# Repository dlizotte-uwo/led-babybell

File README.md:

# led-babybell
LED driver board that plugs into a Pico. Constant current buck using LM3405 and has STEMMA QT connector.

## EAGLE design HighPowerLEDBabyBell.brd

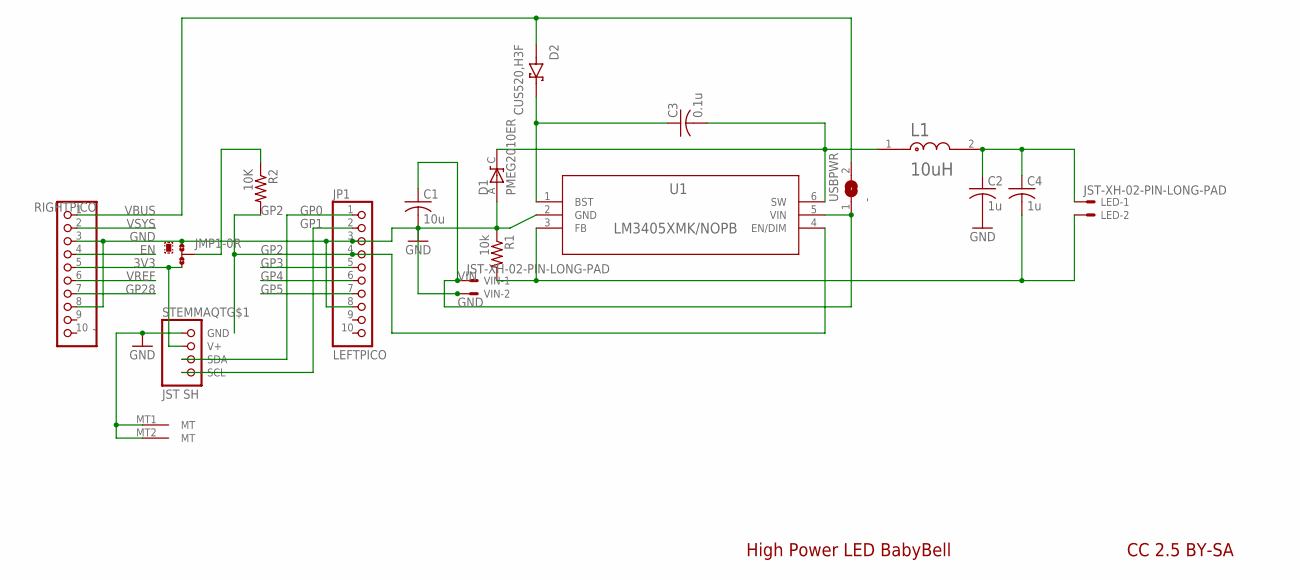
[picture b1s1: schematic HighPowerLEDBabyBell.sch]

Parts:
C1: 10u; C1206
C2, C4: 1u; C1206
C3: 0.1u; C1206
D1: PMEG2010ER; SODFL3517X110N
D2: CUS520,H3F; DIO_CUS520,H3F
JMP1: 0R-JUMPA; A0R-JMP
JP1: LEFTPICO; 1X10
L1: TDK_VLS5045EX-100MTDK_VLS5045EX-100M_0_0; TDK_VLS5045EX-100M_0
LED: JST-XH-02-PIN-LONG-PAD; JST-XH-02-PACKAGE-LONG-PAD
R1: 10k; R1206
R2: 10K; R1206
RIGHTPICO: -; 1X10
STEMMAQT: JST SH; JST_SH4_RA
U1: LM3405XMK/NOPB; MK06A
USBPWR: -; SJ
VIN: JST-XH-02-PIN-LONG-PAD; JST-XH-02-PACKAGE-LONG-PAD

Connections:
3V3: JMP1.3, RIGHTPICO.5, STEMMAQT.2 (V+)
BST: C3.1, D2.C, U1.1 (BST)
EN: RIGHTPICO.4
FB: C4.2, LED.2, R1.2, U1.3 (FB)
GND: C1.2, C2.2, D1.A, JMP1.1, JP1.3, JP1.8, R1.1, RIGHTPICO.3, RIGHTPICO.8, STEMMAQT.1 (GND), STEMMAQT.MT1 (MT), STEMMAQT.MT2 (MT), U1.2 (GND), VIN.2
GP0: JP1.1, STEMMAQT.3 (SDA)
GP1: JP1.2, STEMMAQT.4 (SCL)
GP2: JP1.4, R2.2, U1.4 (EN/DIM)
GP3: JP1.5
GP4: JP1.6
GP5: JP1.7
GP28: RIGHTPICO.7
LED+: C2.1, C4.1, L1.2, LED.1
PUL: JMP1.2, R2.1
SW: C3.2, D1.C, L1.1, U1.6 (SW)
VBUS: D2.A, RIGHTPICO.1, USBPWR.2
VIN: C1.1, U1.5 (VIN), USBPWR.1, VIN.1
VREF: RIGHTPICO.6
VSYS: RIGHTPICO.2

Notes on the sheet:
High Power LED BabyBell
CC 2.5 BY-SA

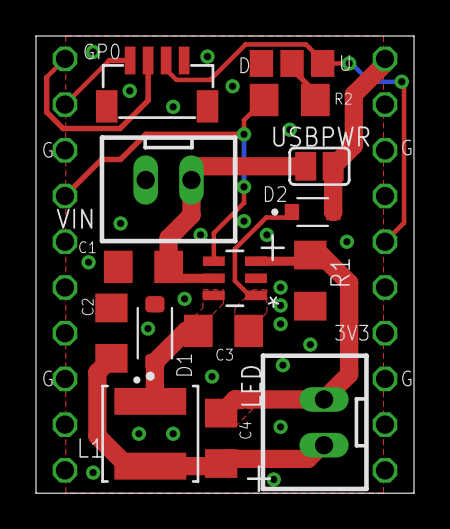
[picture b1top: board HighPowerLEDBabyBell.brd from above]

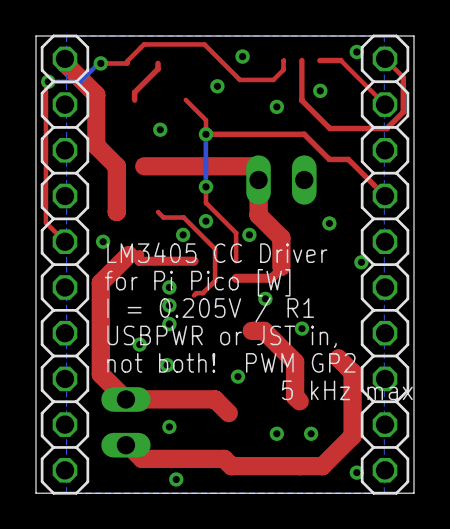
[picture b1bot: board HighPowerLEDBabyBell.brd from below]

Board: 2 copper layers, 21.0 x 25.4 mm, 17 parts (2 on the bottom side), 12 nets.

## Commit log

2023-05-05 Add files via upload
    Eagle schematic and board files

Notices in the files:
parts and their libraries:
microbuilder: This work is placed in the public domain, and may be freely used for commercial and non-commercial work with the following conditions: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
COPYRIGHT: Copyright (C) 2023 Ultra Librarian. All rights reserved.
